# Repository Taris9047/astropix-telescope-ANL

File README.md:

# astropix-telescope

KiCad PCB project for a 4-Layer AstroPix Telescope compatible to AstroPix v2/v3

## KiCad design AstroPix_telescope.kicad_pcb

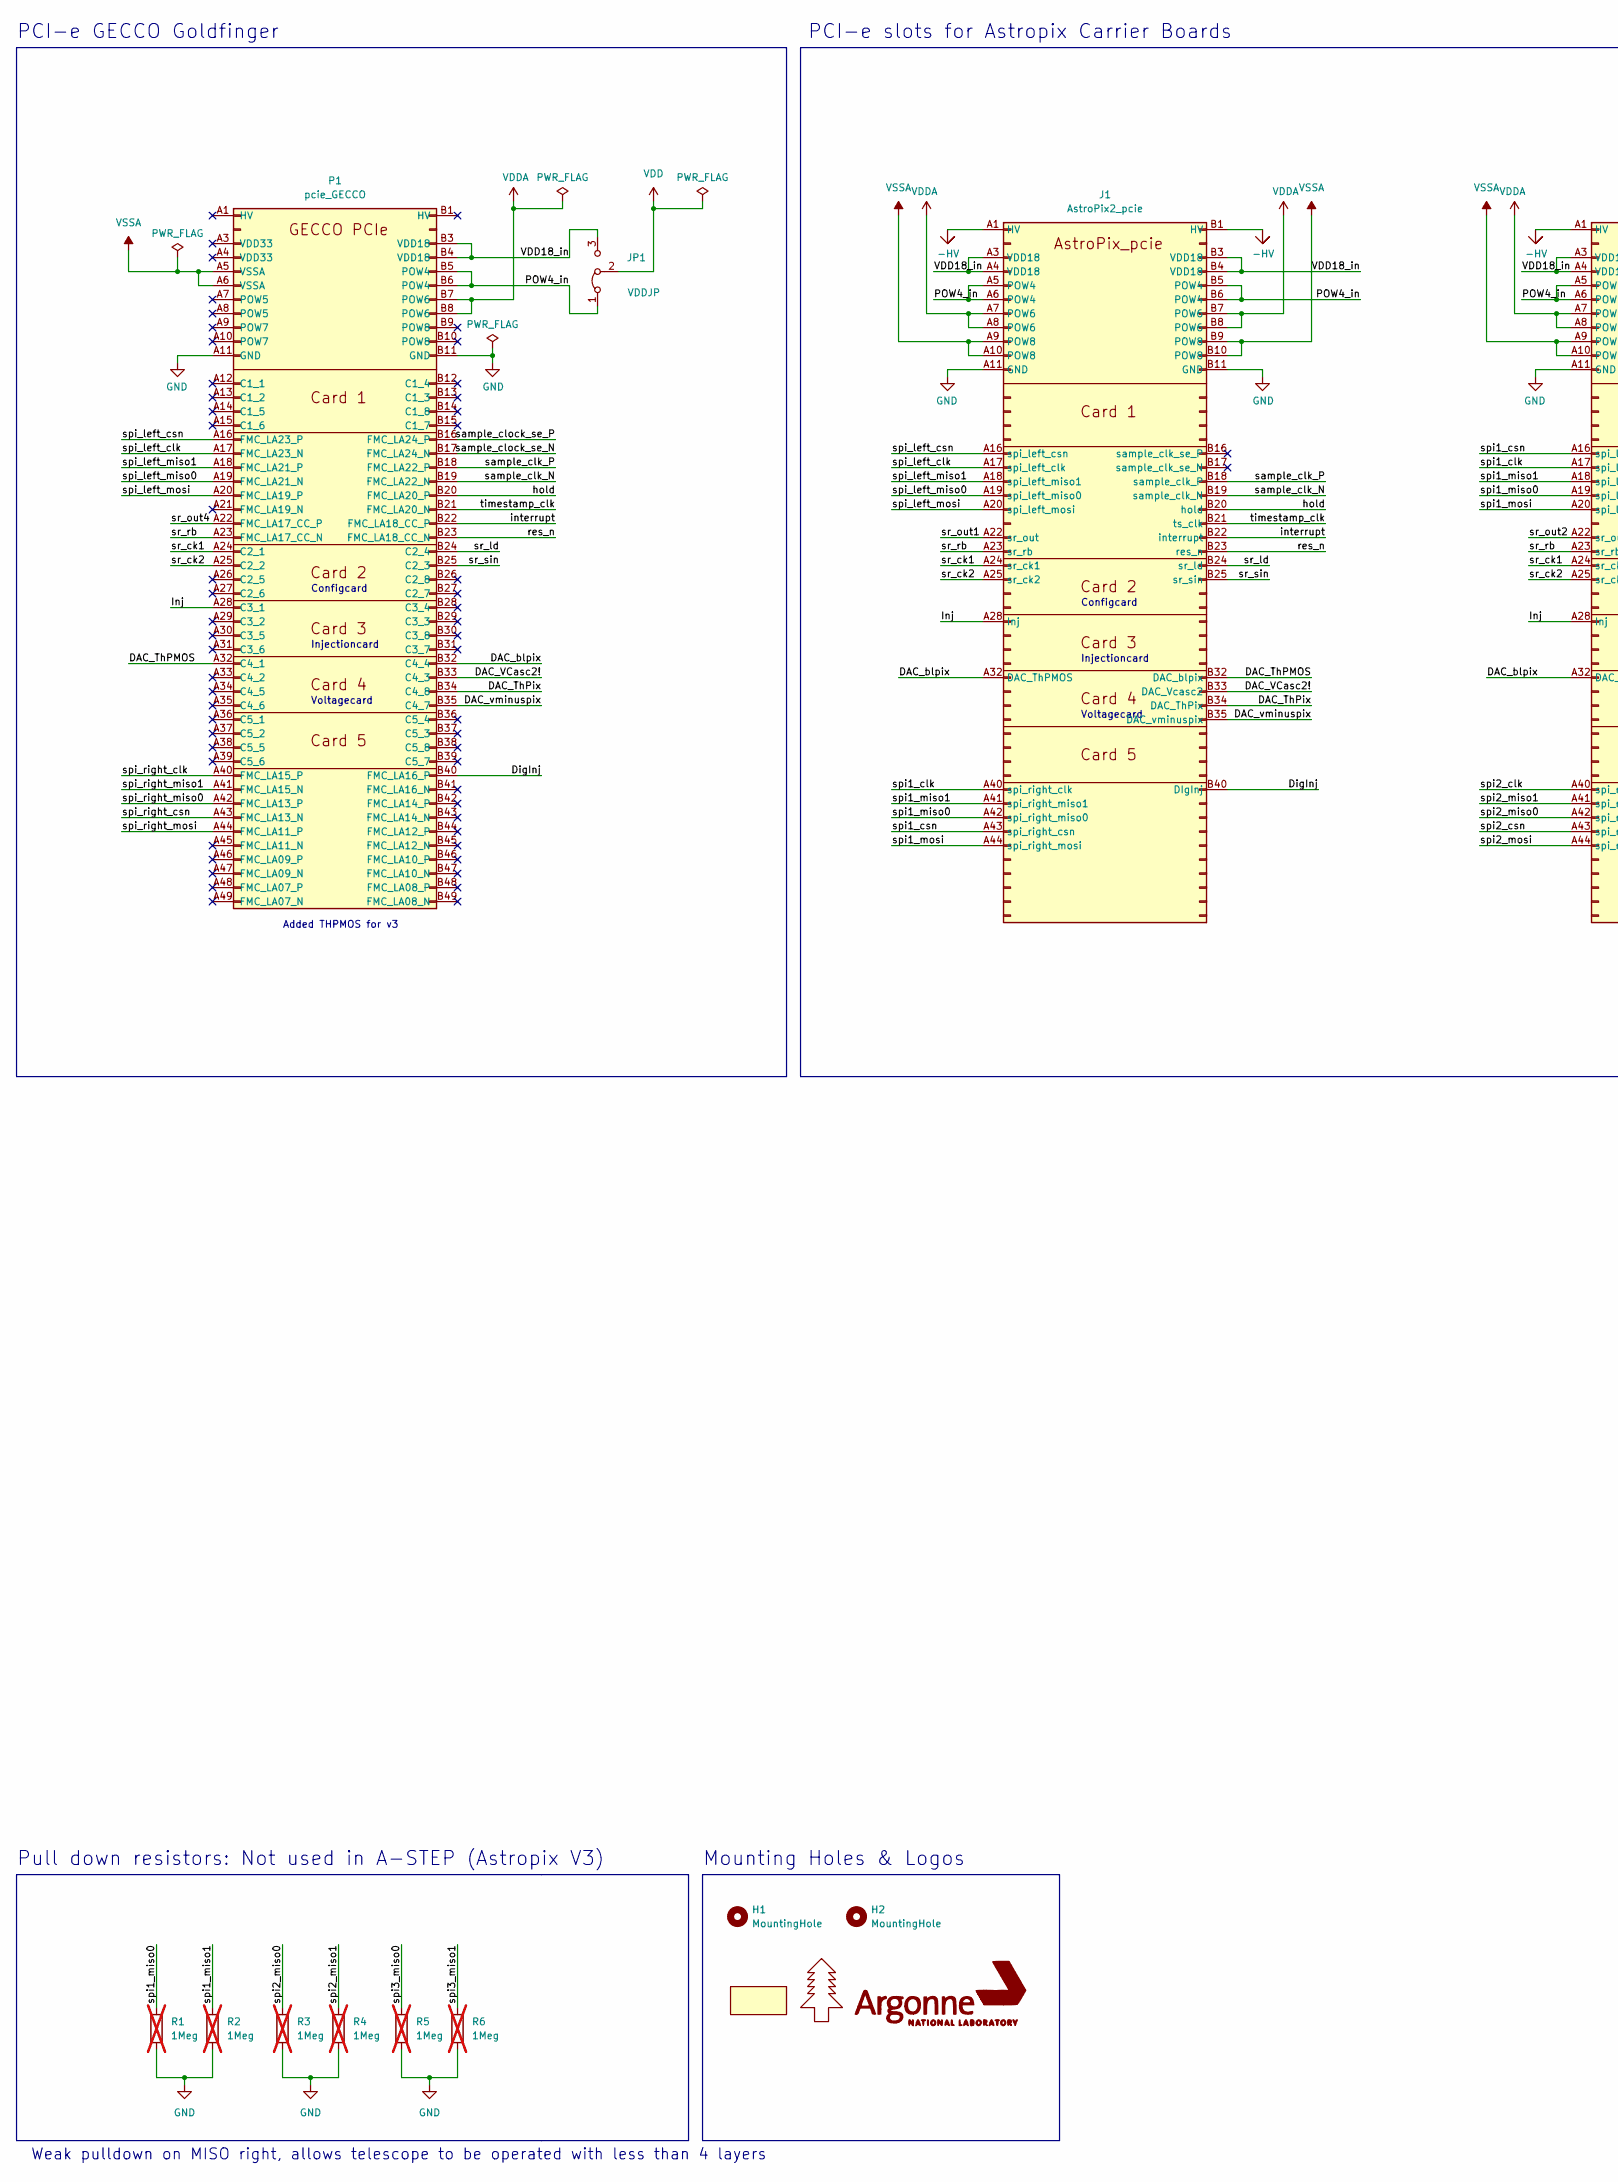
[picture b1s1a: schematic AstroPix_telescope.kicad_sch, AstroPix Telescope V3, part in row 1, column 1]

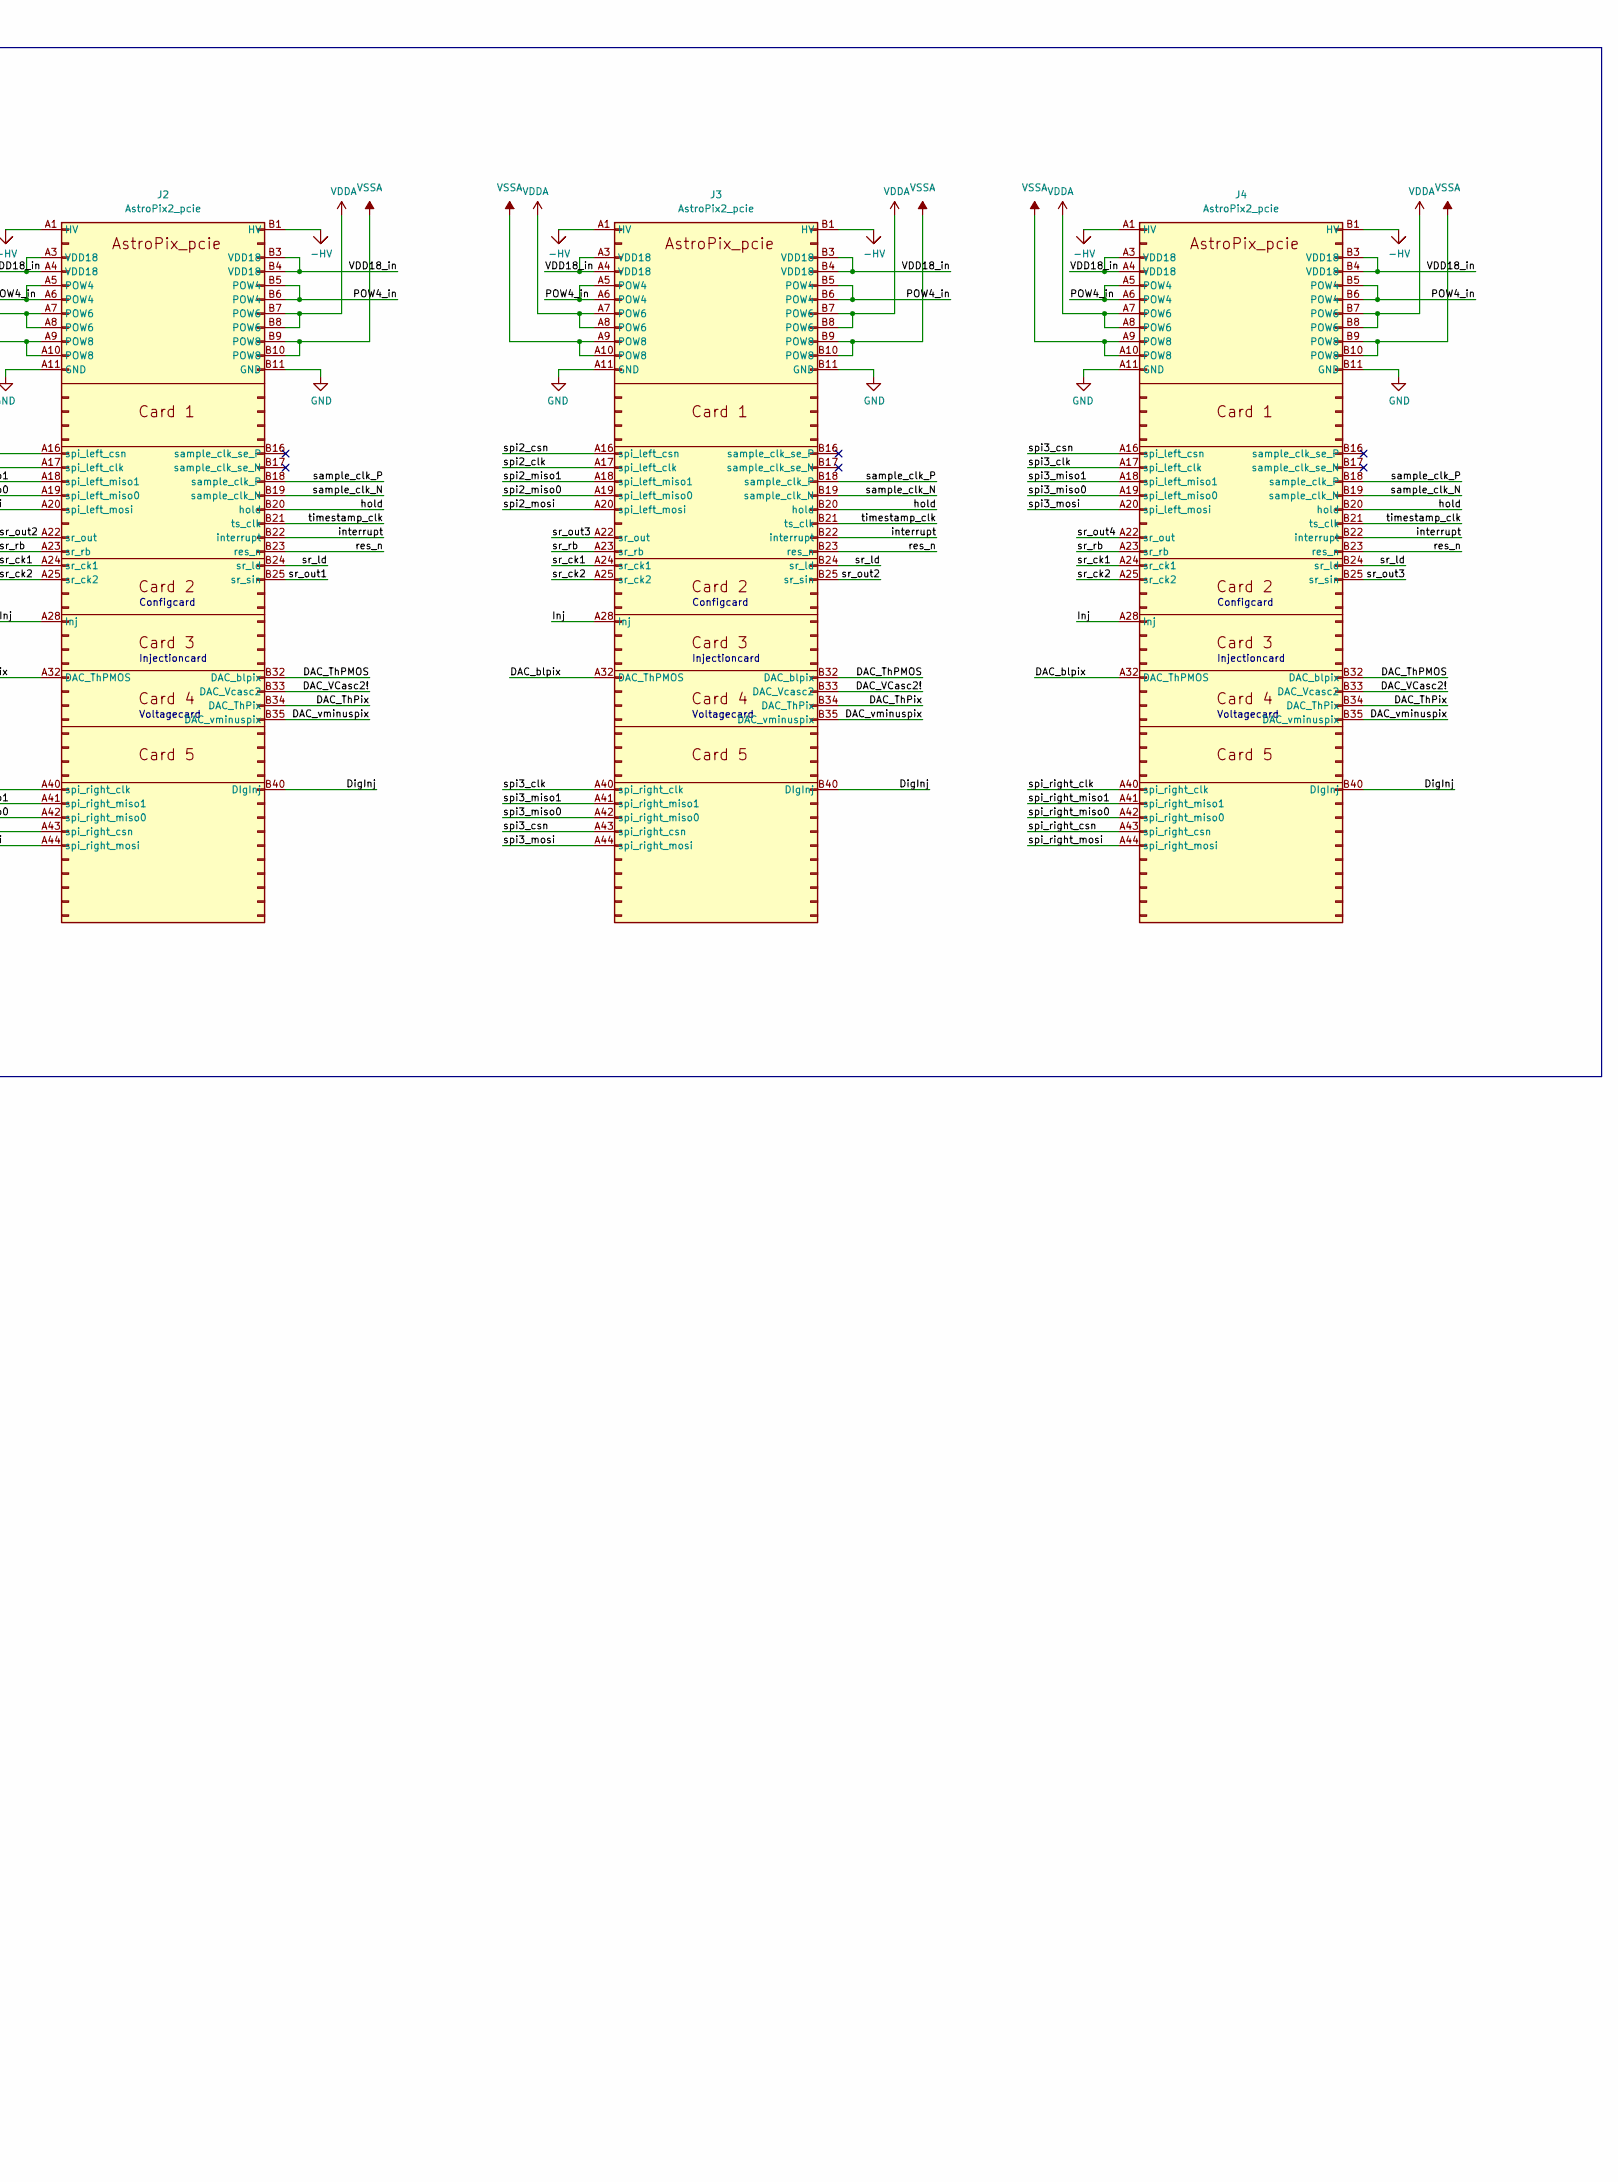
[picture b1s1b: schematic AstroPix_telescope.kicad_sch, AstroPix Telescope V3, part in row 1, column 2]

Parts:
H1, H2: MountingHole; MountingHole_3.2mm_M3_DIN965_Pad
J1, J2, J3, J4: AstroPix2_pcie; SAMTEC_PCIE-098-02-X-D-TH
JP1: VDDJP; PinHeader_1x03_P2.54mm_Vertical
Logo1: KIT_logo; logo
Logo2: SCIPP_Logo
Logo3: ANL_LOGO; ANL_Logo
P1: pcie_GECCO; BUS_PCIexpress_x16_mod
R1, R2, R3, R4, R5, R6: 1Meg; R_0603_1608Metric; not fitted

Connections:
-HV: J1.A1 (HV), J1.B1 (HV), J2.A1 (HV), J2.B1 (HV), J3.A1 (HV), J3.B1 (HV), J4.A1 (HV), J4.B1 (HV)
/DAC_ThPMOS: J1.B32 (DAC_blpix), J2.B32 (DAC_blpix), J3.B32 (DAC_blpix), J4.B32 (DAC_blpix), P1.A32 (C4_1)
/DAC_ThPix: J1.B34 (DAC_ThPix), J2.B34 (DAC_ThPix), J3.B34 (DAC_ThPix), J4.B34 (DAC_ThPix), P1.B34 (C4_8)
/DAC_VCasc2!: J1.B33 (DAC_Vcasc2), J2.B33 (DAC_Vcasc2), J3.B33 (DAC_Vcasc2), J4.B33 (DAC_Vcasc2), P1.B33 (C4_3)
/DAC_blpix: J1.A32 (DAC_ThPMOS), J2.A32 (DAC_ThPMOS), J3.A32 (DAC_ThPMOS), J4.A32 (DAC_ThPMOS), P1.B32 (C4_4)
/DAC_vminuspix: J1.B35 (DAC_vminuspix), J2.B35 (DAC_vminuspix), J3.B35 (DAC_vminuspix), J4.B35 (DAC_vminuspix), P1.B35 (C4_7)
/DigInj: J1.B40 (DIgInj), J2.B40 (DIgInj), J3.B40 (DIgInj), J4.B40 (DIgInj), P1.B40 (FMC_LA16_P)
/Inj: J1.A28 (Inj), J2.A28 (Inj), J3.A28 (Inj), J4.A28 (Inj), P1.A28 (C3_1)
/POW4_in: J1.A5 (POW4), J1.A6 (POW4), J1.B5 (POW4), J1.B6 (POW4), J2.A5 (POW4), J2.A6 (POW4), J2.B5 (POW4), J2.B6 (POW4), J3.A5 (POW4), J3.A6 (POW4), J3.B5 (POW4), J3.B6 (POW4), J4.A5 (POW4), J4.A6 (POW4), J4.B5 (POW4), J4.B6 (POW4), JP1.1 (A), P1.B5 (POW4), P1.B6 (POW4)
/VDD18_in: J1.A3 (VDD18), J1.A4 (VDD18), J1.B3 (VDD18), J1.B4 (VDD18), J2.A3 (VDD18), J2.A4 (VDD18), J2.B3 (VDD18), J2.B4 (VDD18), J3.A3 (VDD18), J3.A4 (VDD18), J3.B3 (VDD18), J3.B4 (VDD18), J4.A3 (VDD18), J4.A4 (VDD18), J4.B3 (VDD18), J4.B4 (VDD18), JP1.3 (B), P1.B3 (VDD18), P1.B4 (VDD18)
/hold: J1.B20 (hold), J2.B20 (hold), J3.B20 (hold), J4.B20 (hold), P1.B20 (FMC_LA20_P)
/interrupt: J1.B22 (interrupt), J2.B22 (interrupt), J3.B22 (interrupt), J4.B22 (interrupt), P1.B22 (FMC_LA18_CC_P)
/res_n: J1.B23 (res_n), J2.B23 (res_n), J3.B23 (res_n), J4.B23 (res_n), P1.B23 (FMC_LA18_CC_N)
/sample_clk_N: J1.B19 (sample_clk_N), J2.B19 (sample_clk_N), J3.B19 (sample_clk_N), J4.B19 (sample_clk_N), P1.B19 (FMC_LA22_N)
/sample_clk_P: J1.B18 (sample_clk_P), J2.B18 (sample_clk_P), J3.B18 (sample_clk_P), J4.B18 (sample_clk_P), P1.B18 (FMC_LA22_P)
/sample_clock_se_N: P1.B17 (FMC_LA24_N)
/sample_clock_se_P: P1.B16 (FMC_LA24_P)
/spi1_clk: J1.A40 (spi_right_clk), J2.A17 (spi_left_clk)
/spi1_csn: J1.A43 (spi_right_csn), J2.A16 (spi_left_csn)
/spi1_miso0: J1.A42 (spi_right_miso0), J2.A19 (spi_left_miso0), R1.1
/spi1_miso1: J1.A41 (spi_right_miso1), J2.A18 (spi_left_miso1), R2.1
/spi1_mosi: J1.A44 (spi_right_mosi), J2.A20 (spi_left_mosi)
/spi2_clk: J2.A40 (spi_right_clk), J3.A17 (spi_left_clk)
/spi2_csn: J2.A43 (spi_right_csn), J3.A16 (spi_left_csn)
/spi2_miso0: J2.A42 (spi_right_miso0), J3.A19 (spi_left_miso0), R3.1
/spi2_miso1: J2.A41 (spi_right_miso1), J3.A18 (spi_left_miso1), R4.1
/spi2_mosi: J2.A44 (spi_right_mosi), J3.A20 (spi_left_mosi)
/spi3_clk: J3.A40 (spi_right_clk), J4.A17 (spi_left_clk)
/spi3_csn: J3.A43 (spi_right_csn), J4.A16 (spi_left_csn)
/spi3_miso0: J3.A42 (spi_right_miso0), J4.A19 (spi_left_miso0), R5.1
/spi3_miso1: J3.A41 (spi_right_miso1), J4.A18 (spi_left_miso1), R6.1
/spi3_mosi: J3.A44 (spi_right_mosi), J4.A20 (spi_left_mosi)
/spi_left_clk: J1.A17 (spi_left_clk), P1.A17 (FMC_LA23_N)
/spi_left_csn: J1.A16 (spi_left_csn), P1.A16 (FMC_LA23_P)
/spi_left_miso0: J1.A19 (spi_left_miso0), P1.A19 (FMC_LA21_N)
/spi_left_miso1: J1.A18 (spi_left_miso1), P1.A18 (FMC_LA21_P)
/spi_left_mosi: J1.A20 (spi_left_mosi), P1.A20 (FMC_LA19_P)
/spi_right_clk: J4.A40 (spi_right_clk), P1.A40 (FMC_LA15_P)
/spi_right_csn: J4.A43 (spi_right_csn), P1.A43 (FMC_LA13_N)
/spi_right_miso0: J4.A42 (spi_right_miso0), P1.A42 (FMC_LA13_P)
/spi_right_miso1: J4.A41 (spi_right_miso1), P1.A41 (FMC_LA15_N)
/spi_right_mosi: J4.A44 (spi_right_mosi), P1.A44 (FMC_LA11_P)
/sr_ck1: J1.A24 (sr_ck1), J2.A24 (sr_ck1), J3.A24 (sr_ck1), J4.A24 (sr_ck1), P1.A24 (C2_1)
/sr_ck2: J1.A25 (sr_ck2), J2.A25 (sr_ck2), J3.A25 (sr_ck2), J4.A25 (sr_ck2), P1.A25 (C2_2)
/sr_ld: J1.B24 (sr_ld), J2.B24 (sr_ld), J3.B24 (sr_ld), J4.B24 (sr_ld), P1.B24 (C2_4)
/sr_out1: J1.A22 (sr_out), J2.B25 (sr_sin)
/sr_out2: J2.A22 (sr_out), J3.B25 (sr_sin)
/sr_out3: J3.A22 (sr_out), J4.B25 (sr_sin)
/sr_out4: J4.A22 (sr_out), P1.A22 (FMC_LA17_CC_P)
/sr_rb: J1.A23 (sr_rb), J2.A23 (sr_rb), J3.A23 (sr_rb), J4.A23 (sr_rb), P1.A23 (FMC_LA17_CC_N)
/sr_sin: J1.B25 (sr_sin), P1.B25 (C2_3)
/timestamp_clk: J1.B21 (ts_clk), J2.B21 (ts_clk), J3.B21 (ts_clk), J4.B21 (ts_clk), P1.B21 (FMC_LA20_N)

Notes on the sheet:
Pull down resistors: Not used in A-STEP (Astropix V3)
Weak pulldown on MISO right, allows telescope to be operated with less than 4 layers
Configcard
Voltagecard
Mounting Holes & Logos
Injectioncard
Added THPMOS for v3
PCI-e GECCO Goldfinger
PCI-e slots for Astropix Carrier Boards

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
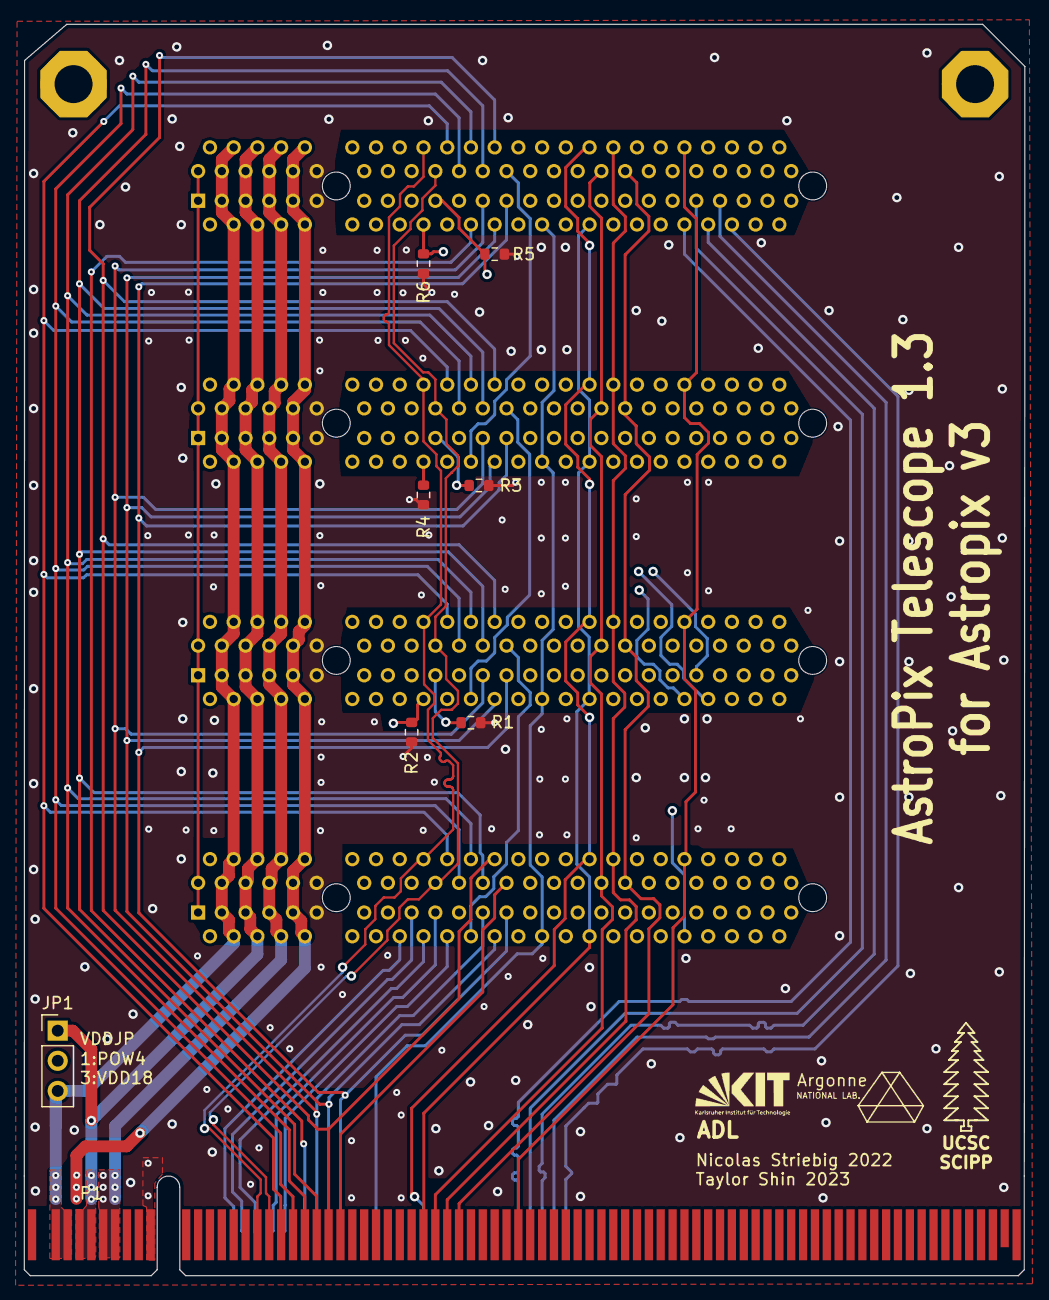
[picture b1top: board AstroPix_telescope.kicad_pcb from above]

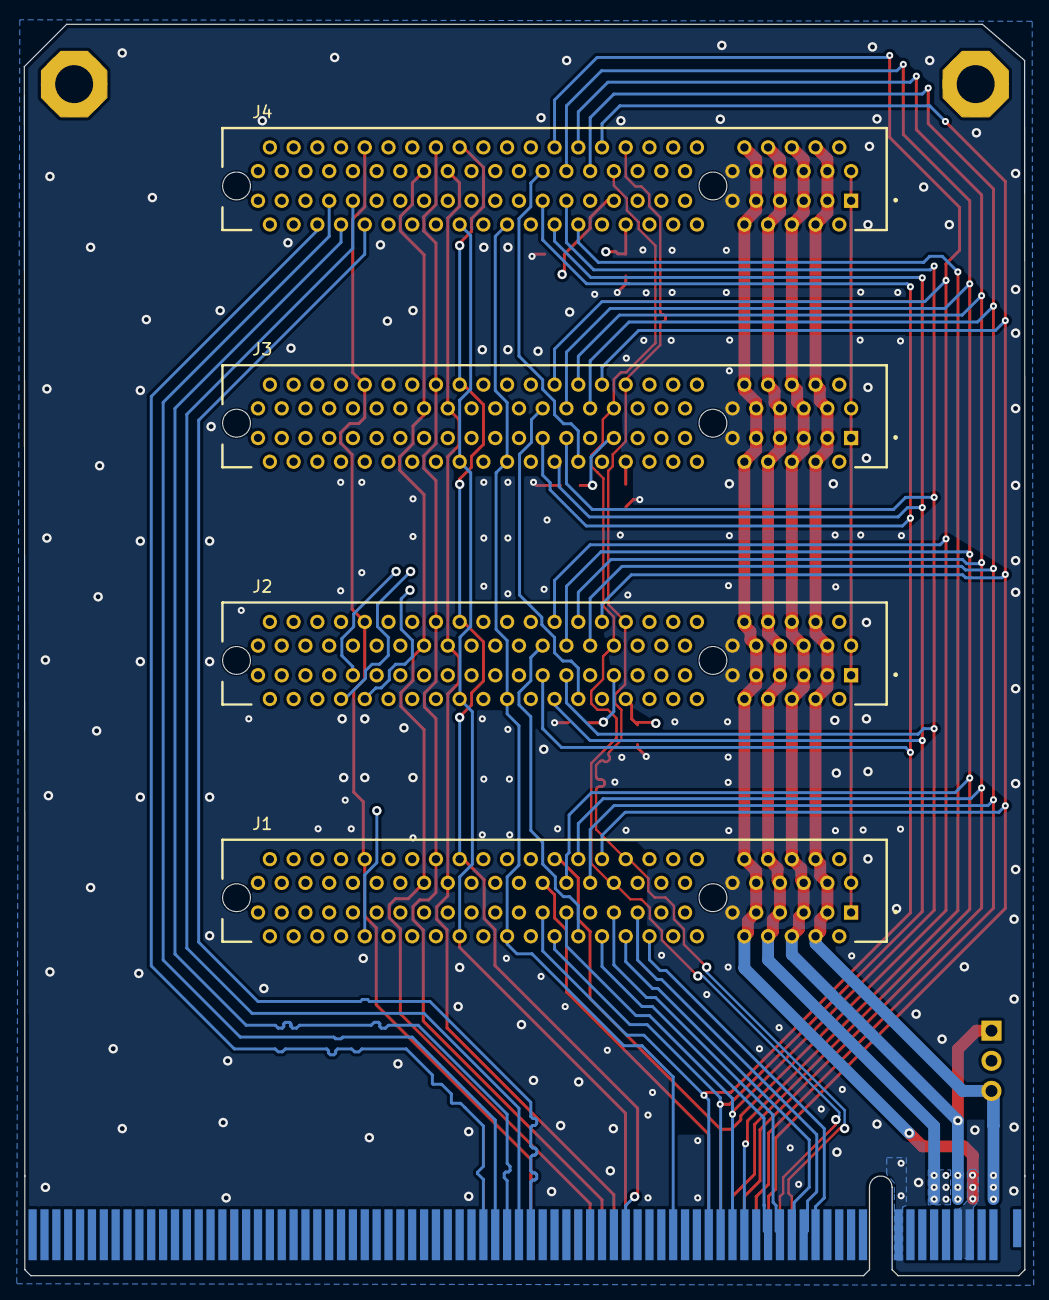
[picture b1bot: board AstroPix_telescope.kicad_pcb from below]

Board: 4 copper layers, 84.4 x 105.5 mm, 17 parts (4 on the bottom side), 53 nets.

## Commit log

2022-10-12 Ignore backups
2022-10-12 Added custom pcie x16 footprint
2022-10-12 Added Logo + minor improvements
2022-10-12 Added schematic pdf
2022-10-12 Layout minor improvements
2022-10-14 Added signal thPMOS, viastitching and removed unused rings
2022-10-14 Updated schematic pdf
2022-11-14 Added VSSA for Astropix3
2023-01-20 Applied most of corrections.
    And re-verified the 100 Ohm characteristic impedance.
2023-01-20 Added 3D shots..
2023-01-20 Resolved spaghetti madness and matched line length as much as possible.
    Fabrication outputs prepared, yet again.
2023-01-25 Updated with normalized differential pair length for each PCI-e ports.
2023-01-25 1. Removed some acute corners at the differential pair lines of the first PCI-e connector. 2. Added Preliminary 3D shot. 3. Updated Fabrication Outputs.
2023-01-25 Zipped Fabrication output added.
2023-01-25 1. Zipped most recent fabrication output. 2. Moved Fabrication output zip directory.
2023-01-26 Trigger board merged and prepared another fabrication output.
2023-03-02 Migrated to KiCAD 7
2023-09-16 New Branch Added..
2023-09-16 New revision.
2023-09-19 Preliminary design...
2023-09-19 .gitignore updated...
2023-09-20 V3 initial commit for fabrication.
